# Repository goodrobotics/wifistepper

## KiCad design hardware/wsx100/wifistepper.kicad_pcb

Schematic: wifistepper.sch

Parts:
C1: 22uF; C_1206_3216Metric
C2, C3: 470nF 100V; C_0805_2012Metric
C4: 220nF; C_0805_2012Metric
C5, C12, C14, C16, C17, C21, C22, C23, C24: 0.1uF; C_0603_1608Metric
C6, C7, C8, C9: 220nF 100V; C_0805_2012Metric
C10, C11: 100uF 100V (Low ESR); CP_Radial_D12.5mm_P5.00mm
C13: 47nF 100V; C_0805_2012Metric
C15, C20: 10uF; C_0805_2012Metric
C18: 1uF 100V; C_0805_2012Metric
C19: 1uF; C_0603_1608Metric
D0: 80V (Back EMF Clamp); D_SMB
D1: D_Schottky_x2_Serial_AKC; SOT-23
D2: D_Schottky; D_SOD-123
D3: LED GRN; D_0805_2012Metric
D4: LED YEL; D_0805_2012Metric
D5: LED RED; D_0805_2012Metric
D6: 3.9V; D_SOD-123
D7: 50V Clamp; D_SMF_DO-219AB
FB1: Ferrite_Bead_Small; L_0603_1608Metric
J1: Barrel_Jack_Switch; BarrelJack_Horizontal
J2: Screw_Terminal; TerminalBlock_Phoenix_PT-1,5-6-5.0-H_1x06_P5.00mm_Horizontal
J3, J4: Conn_01x10; PinHeader_1x10_P2.54mm_Vertical
J5: Conn_01x02; PinHeader_1x02_P2.54mm_Vertical
JP0, JP3: SolderJumper_2_Bridged; SolderJumper-2_P1.3mm_Bridged_RoundedPad1.0x1.5mm
JP1, JP2: Jumper_2_Open; STpowerSTEP01_JMP
JP4: SolderJumper_3_Bridged12; SolderJumper-3_P1.3mm_Bridged12_RoundedPad1.0x1.5mm
L1: 33uH; L_Taiyo-Yuden_NR-50xx
R1: -; Resistor_NP_0805
R2, R16, R17, R18, R19, R20, R21, R23, R24, R25, R26, R27, R28, R29: 22; R_0603_1608Metric
R3: 47K; R_0603_1608Metric
R4: 1.8K; R_0603_1608Metric
R5, R14, R15: 2.2K; R_0603_1608Metric
R6, R22: 1K; R_0603_1608Metric
R7, R8: 39K; R_0603_1608Metric
R9, R10, R11: 330; R_0603_1608Metric
R12, R13: 10K; R_0603_1608Metric
RS1, RS2, RS3, RS4, RS5, RS6, RS7, RS8: 0.27; R_2512_6332Metric
SW1: SW_SPST; TL3315NF100Q
U1: ESP-WROOM-02
U2: powerSTEP01
U3: MAX15062A; DFN-8_2x2mm_P0.5mm
U4: ATECC508A; SOIC-8_3.9x4.9mm_P1.27mm

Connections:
+3V3: C1.1, C4.1, C12.1, C15.1, C16.1, C20.1, C21.2, C22.1, D2.2 (A), D3.2 (A), D4.2 (A), D5.2 (A), J3.1, J4.1, L1.1, R7.1, R8.1, R13.2, R14.1, R15.1, U1.1, U2.13, U2.60, U2.62, U3.4 (FB/Vout), U4.8
AUTH_SCK: R15.2, R27.2, SW1.2 (B), U1.14, U4.6
AUTH_SDA: R14.2, R26.2, U1.7, U4.5
GND: C1.2, C2.2, C4.2, C5.2, C6.2, C7.2, C8.2, C9.2, C10.2, C11.2, C12.2, C14.2, C15.2, C16.2, C17.2, C18.2, C19.2, C20.2, C21.1, C22.2, C23.2, C24.2, D0.2 (A), D6.2 (A), D7.2 (A), J1.2, J2.6, J3.2, J4.2, J5.2, JP1.2 (B), JP2.2 (B), R4.2, R6.2, R11.2, R12.2, RS1.1, RS2.1, RS3.1, RS4.1, RS5.1, RS6.1, RS7.1, RS8.1, SW1.1 (A), U1.9, U1.13, U1.18, U1.19, U2.8, U2.21, U2.59, U2.E9, U3.7 (GND), U4.4; also elsewhere on the board
unnamed: C2.1, D2.1 (K), U2.58
unnamed: C3.1, D1.2 (K), U2.56
unnamed: C13.1, U2.57
unnamed: C13.2, D1.3 (common)
unnamed: C17.1, R13.1, U1.2
unnamed: C19.1, U3.3 (VCC)
unnamed: D3.1 (K), R11.1
unnamed: D4.1 (K), R10.1
unnamed: D5.1 (K), R9.1
unnamed: J3.3, R22.1
unnamed: J3.4, R23.1
unnamed: J3.5, R24.1
unnamed: J3.6, R25.1
unnamed: J3.7, R16.1
unnamed: J3.8, R17.1
unnamed: J3.9, R2.1
unnamed: J3.10, R29.1
unnamed: J4.3, R26.1
unnamed: J4.4, R27.1
unnamed: J4.5, R18.1
unnamed: J4.6, R5.1
unnamed: J4.7, R19.1
unnamed: J4.8, R28.1
unnamed: J4.9, R20.1
unnamed: J4.10, R21.1
unnamed 30: JP0.1 (A); also elsewhere on the board
unnamed: JP1.1 (A), RS1.2, RS2.2, RS3.2, RS7.2, U2.20, U2.E10, U2.E11
unnamed: JP2.1 (A), RS4.2, RS5.2, RS6.2, RS8.2, U2.9, U2.E12, U2.E13
unnamed: JP4.1 (A), R3.2
unnamed: JP4.3 (B), R1.2
unnamed: L1.2, U3.8 (LX)
OUTA1: J2.3, U2.38, U2.42, U2.53, U2.E4
OUTA2: J2.4, U2.22, U2.33, U2.37, U2.E3
OUTB1: J2.2, U2.65, U2.76, U2.80, U2.E7
OUTB2: J2.1, U2.7, U2.81, U2.85, U2.E8
PROG_BOOT: R28.2, U1.8
PROG_RX: R20.2, U1.11
PROG_TX: R21.2, U1.12
SM_ADC: C5.1, JP4.2 (C), R4.1, U2.54
SM_BUSY: R7.2, R25.2, U2.15
SM_CLK: R16.2, U1.3, U2.11
SM_CS: R29.2, U1.10, U2.10
SM_FLAG: R8.2, R9.2, R24.2, U2.16
SM_RST: C14.1, R12.1, U1.6, U2.19
SM_SI: R17.2, U1.5, U2.12
SM_SO: R2.2, U1.4, U2.14
SM_STCLK: C24.1, R23.2, U2.17
SM_SW: C23.1, D6.1 (K), R22.2, U2.18
WIFI_ADC: R5.2, R6.1, U1.16
WIFI_CONN: JP3.1 (A), R10.2
WIFI_GPIO: JP3.2 (B), R19.2, U1.17
WIFI_RST: R18.2, U1.15

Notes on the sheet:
Wi-Fi Stepper
Andrew Klofas <andrew@goodrobotics.net>
02/04/2019

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
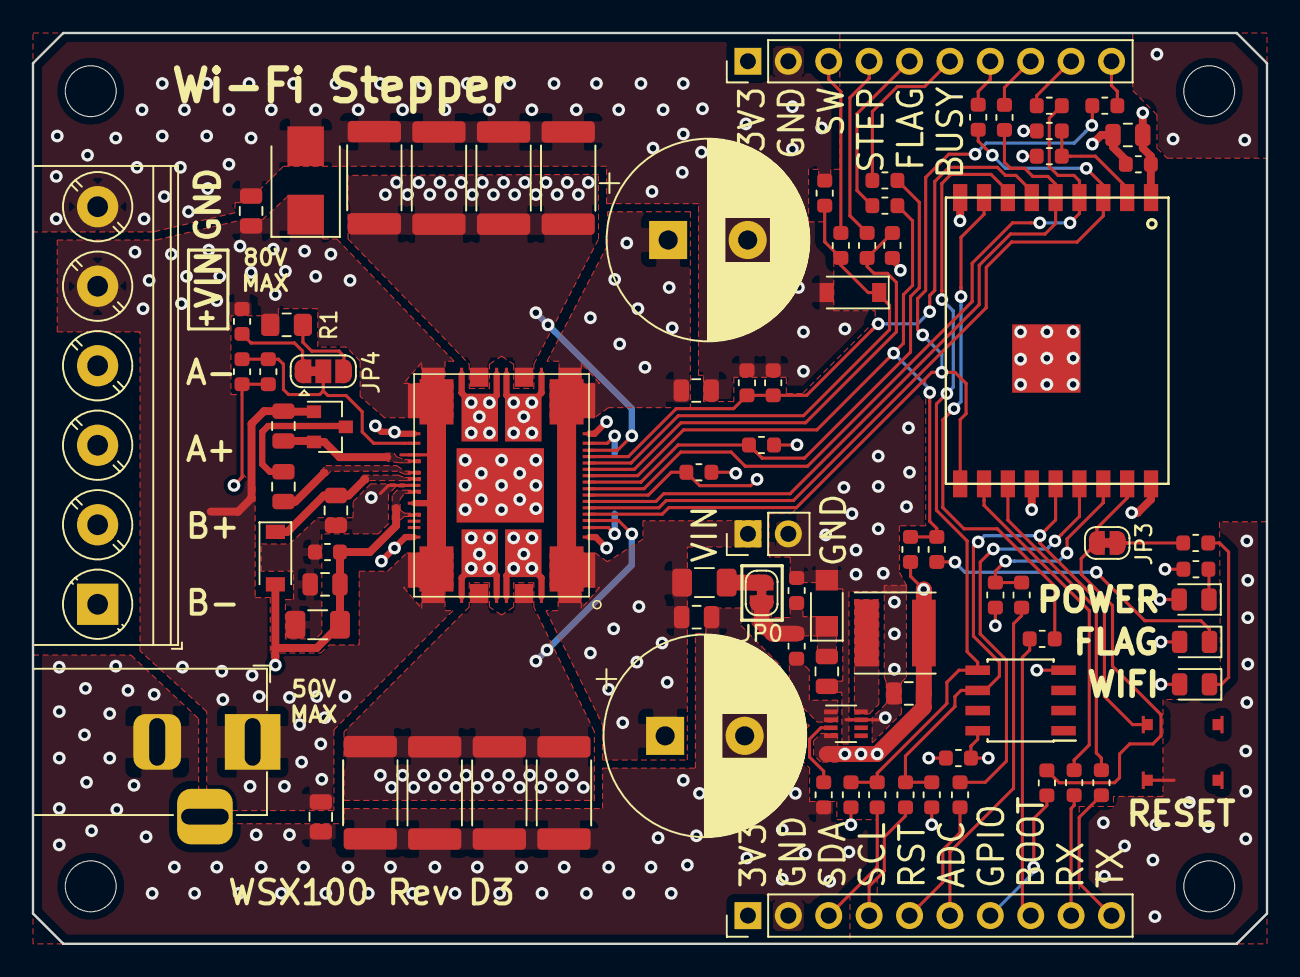
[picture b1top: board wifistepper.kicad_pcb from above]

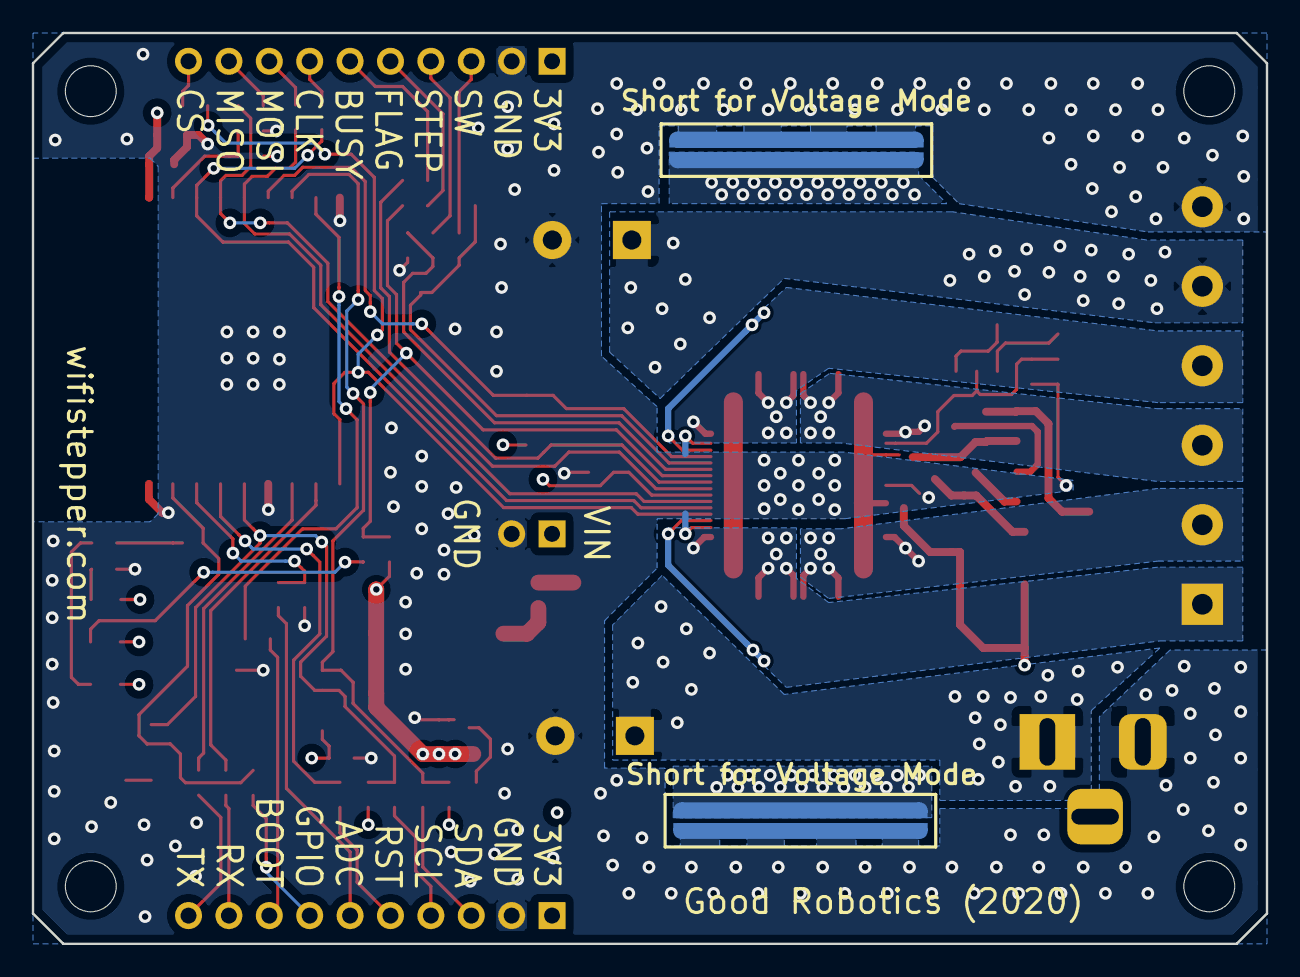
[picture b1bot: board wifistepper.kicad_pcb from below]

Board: 4 copper layers, 77.6 x 57.3 mm, 88 parts (2 on the bottom side), 59 nets.

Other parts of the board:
R30: 10; R_1206_3216Metric
R31: 47K; R_0603_1608Metric
R32: 000; R_0603_1608Metric

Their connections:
GND: R31.1; also elsewhere on the board
unnamed 30: R30.1; also elsewhere on the board

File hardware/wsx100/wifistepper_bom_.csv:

Component,Description,Part,References,Value,Footprint,Quantity Per PCB,Datasheet
1,Unpolarized capacitor,C,C5 C12 C14 C16 C17 C21 C22 C23 C24,0.1uF,C_0603_1608Metric,9,~
2,Polarized capacitor,CP,C10 C11,100uF 100V (Low ESR),CP_Radial_D12.5mm_P5.00mm,2,~
3,Unpolarized capacitor,C,C15 C20,10uF,C_0805_2012Metric,2,~
4,Unpolarized capacitor,C,C19,1uF,C_0603_1608Metric,1,~
5,Unpolarized capacitor,C,C18,1uF 100V,C_0805_2012Metric,1,~
6,Unpolarized capacitor,C,C4,220nF,C_0805_2012Metric,1,~
7,Unpolarized capacitor,C,C6 C7 C8 C9,220nF 100V,C_0805_2012Metric,4,~
8,Polarized capacitor,CP,C1,22uF,C_1206_3216Metric,1,~
9,Unpolarized capacitor,C,C2 C3,470nF 100V,C_0805_2012Metric,2,~
10,Unpolarized capacitor,C,C13,47nF 100V,C_0805_2012Metric,1,~
11,Zener diode,D_Zener,D6,3.9V,D_SOD-123,1,~
12,Schottky diode,D_Schottky,D0,80V (Back EMF Clamp),D_SOD-123F,1,~
13,Schottky diode,D_Schottky,D2,D_Schottky,D_SOD-123,1,~
14,"Dual Schottky diode, anode/cathode/center",D_Schottky_x2_Serial_AKC,D1,D_Schottky_x2_Serial_AKC,SOT-23,1,~
15,Light emitting diode,LED,D3,LED GRN,D_0805_2012Metric,1,~
16,Light emitting diode,LED,D5,LED RED,D_0805_2012Metric,1,~
17,Light emitting diode,LED,D4,LED YEL,D_0805_2012Metric,1,~
18,"Ferrite bead, small symbol",Ferrite_Bead_Small,FB1,Ferrite_Bead_Small,L_0603_1608Metric,1,~
19,DC Barrel Jack with an internal switch,Barrel_Jack_Switch,J1,Barrel_Jack_Switch,BarrelJack_Horizontal,1,~
20,"Generic connector, single row, 01x02, script generated (kicad-library-utils/schlib/autogen/connector/)",Conn_01x02,J5,Conn_01x02,PinHeader_1x02_P2.54mm_Vertical,1,~
21,"Generic connector, single row, 01x09, script generated (kicad-library-utils/schlib/autogen/connector/)",Conn_01x09,J3,Conn_01x09,PinHeader_1x09_P2.54mm_Vertical,1,~
22,"Generic connector, single row, 01x10, script generated (kicad-library-utils/schlib/autogen/connector/)",Conn_01x10,J4,Conn_01x10,PinHeader_1x10_P2.54mm_Vertical,1,~
23,"Generic screw terminal, single row, 01x06, script generated (kicad-library-utils/schlib/autogen/connector/)",Screw_Terminal_01x06,J2,Screw_Terminal,"TerminalBlock_Phoenix_PT-1,5-6-5.0-H_1x06_P5.00mm_Horizontal",1,~
24,"Jumper, 2-pole, open",Jumper_2_Open,JP1 JP2,Jumper_2_Open,STpowerSTEP01_JMP,2,~
25,Inductor,L,L1,33uH,L_Taiyo-Yuden_NR-50xx,1,~
26,Resistor,R,R1,-,Resistor_NP_0805,1,~
27,Resistor,R,R4,1.8K,R_0603_1608Metric,1,~
28,Resistor,R,R12 R13,10K,R_0603_1608Metric,2,~
29,Resistor,R,R6 R22,1K,R_0603_1608Metric,2,~
30,Resistor,R,R5 R14 R15,2.2K,R_0603_1608Metric,3,~
31,Resistor,R,R2 R16 R17 R18 R19 R20 R21 R23 R24 R25 R26 R27 R28,22,R_0603_1608Metric,13,~
32,Resistor,R,R9 R10 R11,330,R_0603_1608Metric,3,~
33,Resistor,R,R7 R8,39K,R_0603_1608Metric,2,~
34,Resistor,R,R3,47K,R_0603_1608Metric,1,~
35,Resistor,R,RS1 RS2 RS3 RS4 RS5 RS6 RS7 RS8,0.27,R_2512_6332Metric,8,~
36,Single Pole Single Throw (SPST) switch,SW_SPST,SW1,SW_SPST,TL3315NF100Q,1,
37,,ATECC508A,U4,ATECC508A,SOIC-8_3.9x4.9mm_P1.27mm,1,
38,,ESP-WROOM-02,U1,ESP-WROOM-02,ESP-WROOM-02,1,
39,"60V, 300mA, synchronous step-down dc-dc converter, 3.3V fixed output voltage, DFN-8",MAX15062A,U3,MAX15062A,DFN-8_2x2mm_P0.5mm,1,http://datasheets.maximintegrated.com/en/ds/MAX15062.pdf
40,,powerSTEP01,U2,powerSTEP01,powerSTEP01,1,





Component Groups:,40
Component Count:,81
Fitted Components:,81
Number of PCBs:,1
Total components:,81
Schematic Version:,
Schematic Date:,
BoM Date:,Thu 07 Feb 2019 08:11:53 PM PST
Schematic Source:,/home/aklofas/Projects/wifistepper/hardware/wsx100/wifistepper.sch
KiCad Version:,Eeschema 5.0.2-bee76a0~70~ubuntu16.04.1

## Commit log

2019-05-27 Initial upload of files
2019-06-04 Updated documentation
2019-06-20 Updated documentation and firmware to version 2
2019-07-09 Added hardware CAD, bugfixes, and documentation tweaks
2020-11-27 Initial Commit of Powershell Module files
2020-11-30 Updated fuctions to be more robust
2020-12-01 Updated with Target parameter
2020-12-02 First Pull Request to Main Site
2020-12-03 Export All Functions from Module with wildcard
2020-12-18 Added move-stepperEstop functions
2021-01-09 Forced Postiion math with angles to trunctate to INT for absolute position, Fixes Move-stepper motor fail when End Postion is not equal to Commanded position
2021-05-19 Board design update with more firmware features
2024-01-19 Fix for Python3
